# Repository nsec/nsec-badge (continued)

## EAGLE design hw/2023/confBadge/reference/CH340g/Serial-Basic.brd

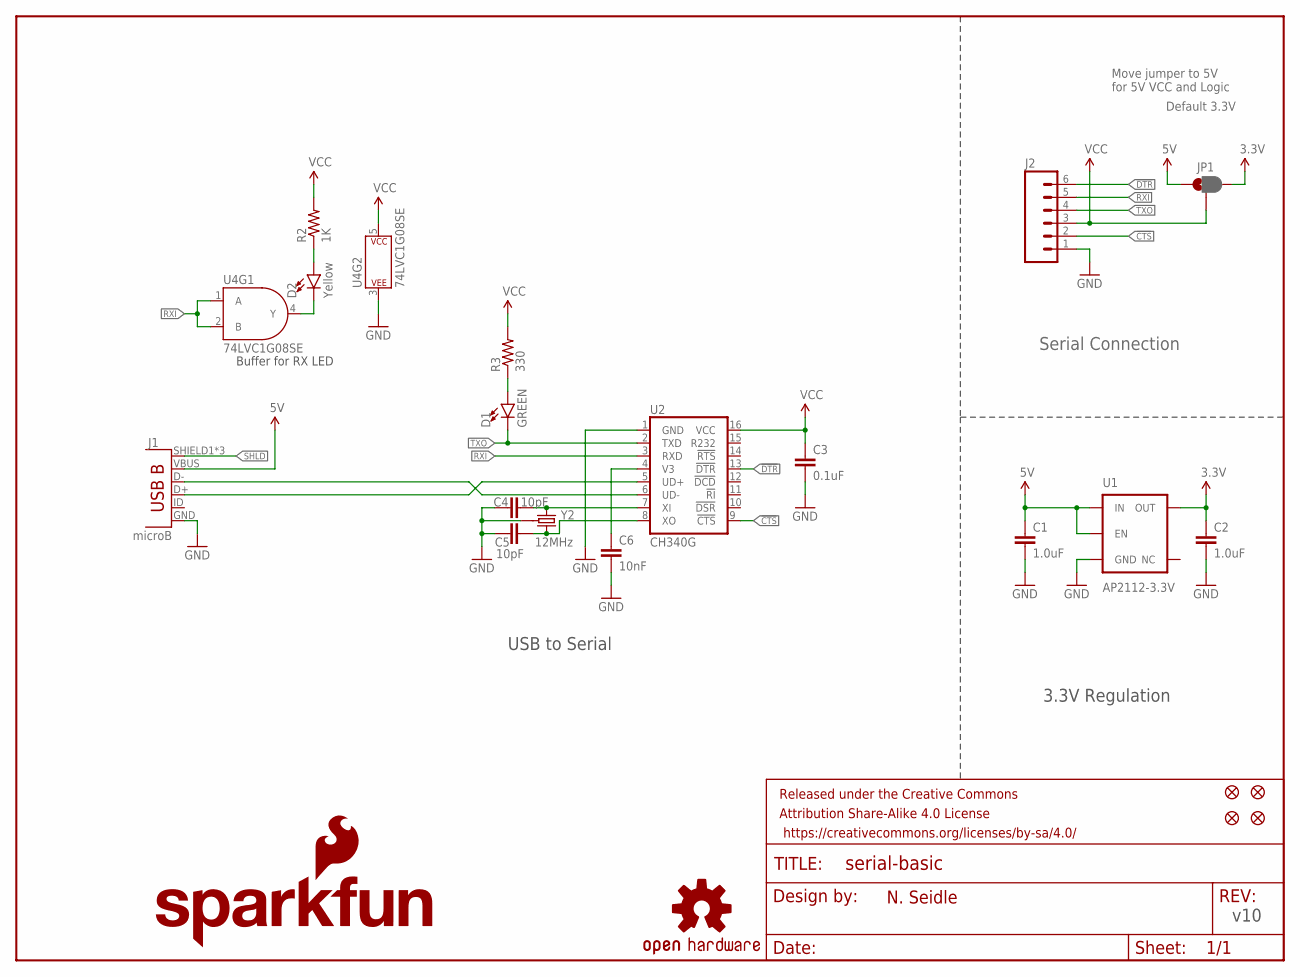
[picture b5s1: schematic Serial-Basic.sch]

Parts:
C1, C2: 1.0uF; 0603-CAP
C3: 0.1uF; 0603-CAP
C4, C5: 10pF; 0603-CAP
C6: 10nF; 0603-CAP
D1: GREEN; LED-0603
D2: Yellow; LED-0603
FRAME1: FRAME-LETTER; CREATIVE_COMMONS
J1: microB; USB-B-MICRO-SMD_V03
J2: M06SMD-FEMALE-V2; 1X06-SMD-FEMALE-V2
JP1: JUMPER-PAD-3-2OF3_NC_BY_PASTE; PAD-JUMPER-3-2OF3_NC_BY_PASTE_YES_SILK_FULL_BOX
JP3, JP4, JP5, JP6: FIDUCIAL1X2; FIDUCIAL-1X2
LOGO1: OSHW-LOGOS; OSHW-LOGO-S
LOGO2: SFE_LOGO_FLAME.1_INCH; SFE_LOGO_FLAME_.1
LOGO3: SFE_LOGO_NAME.1_INCH; SFE_LOGO_NAME_.1
R2: 1K; 0603-RES
R3: 330; 0603-RES
U1: AP2112-3.3V; SOT23-5
U2: CH340G; SO016
U4: 74LVC1G08SE; SOT353
Y2: 12MHz; CRYSTAL-SMD-3.2X2.5

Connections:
3.3V: C2.1, JP1.3, U1.5 (OUT)
5V: C1.1, J1.VBUS, JP1.1, U1.1 (IN), U1.3 (EN)
!CTS: J2.2, U2.9 (!CTS)
!DTR: J2.6, U2.13 (!DTR)
GND: C1.2, C2.2, C3.2, C4.1, C5.1, C6.2, J1.GND, J2.1, U1.2 (GND), U2.1 (GND), U4.3 (P$V-), Y2.2 (GND), Y2.4 (GND)
unnamed: D1.A, R3.1
unnamed: D2.A, R2.1
unnamed: C5.2, U2.8 (XO), Y2.3 (2)
unnamed: C4.2, U2.7 (XI), Y2.1
unnamed: D2.C, U4.4 (Y)
unnamed: J1.D-, U2.6 (UD-)
unnamed: J1.D+, U2.5 (UD+)
RXI: J2.5, U2.3 (RXD), U4.1 (A), U4.2 (B)
SHLD: J1.SHIELD1 (SHIELD), J1.SHIELD2 (SHIELD), J1.SHIELD3 (SHIELD)
TXO: D1.C, J2.4, U2.2 (TXD)
V3: C6.1, U2.4 (V3)
VCC: C3.1, J2.3, JP1.2, R2.2, R3.2, U2.16 (VCC), U4.5 (P$V+)

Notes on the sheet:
Default 3.3V
v10
USB to Serial
3.3V Regulation
N. Seidle
Move jumper to 5V for 5V VCC and Logic
Buffer for RX LED
Serial Connection

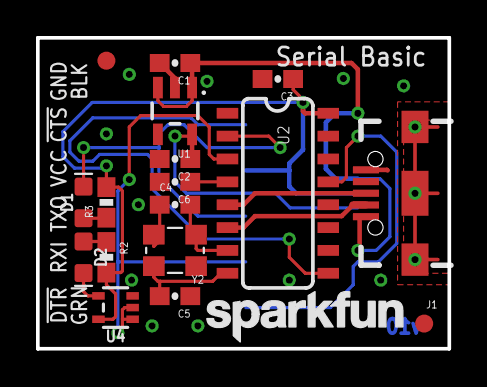
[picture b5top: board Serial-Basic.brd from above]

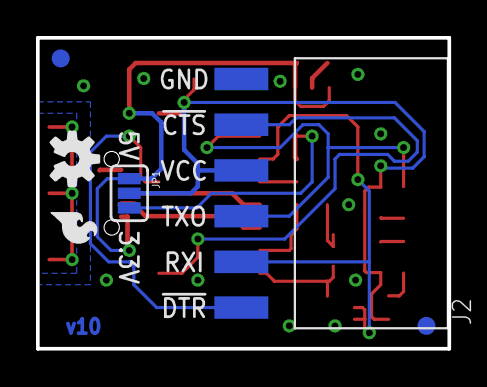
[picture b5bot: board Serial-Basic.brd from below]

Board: 2 copper layers, 22.9 x 17.3 mm, 25 parts (6 on the bottom side), 17 nets.

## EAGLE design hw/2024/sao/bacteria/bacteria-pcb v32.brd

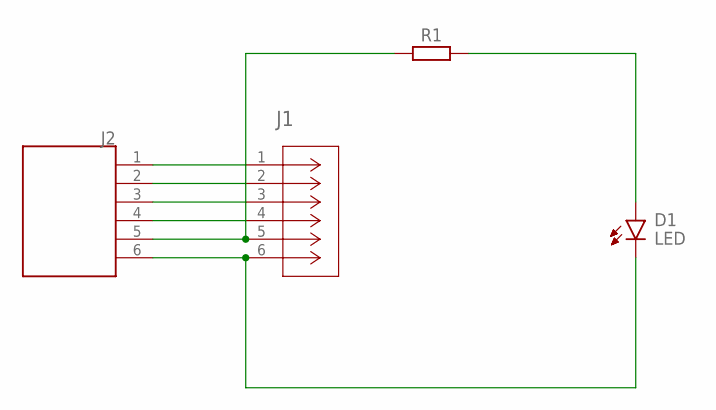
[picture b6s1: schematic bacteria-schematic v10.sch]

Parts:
D1: LED; LEDC3216X75N_FLAT-R
J1: M20-8760342CONN6_M20-8760342_HRW; CONN6_M20-8760342_HRW
J2: SAOPADBREAKOUT
R1: R_CHIP-1206(3216-METRIC); RESC3216X70

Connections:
3V3: J1.5, J2.5, R1.1
GND: D1.C, J1.6, J2.6
GPIO1: J1.1, J2.1
GPIO2: J1.2, J2.2
unnamed: D1.A, R1.2
SCL: J1.4, J2.4
SDA: J1.3, J2.3

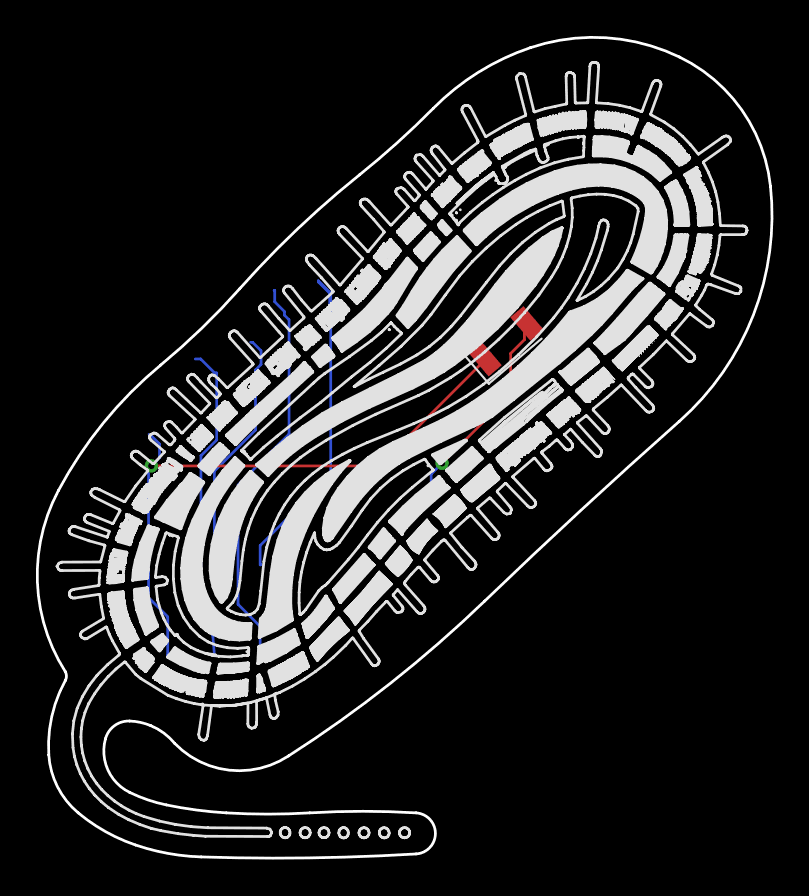
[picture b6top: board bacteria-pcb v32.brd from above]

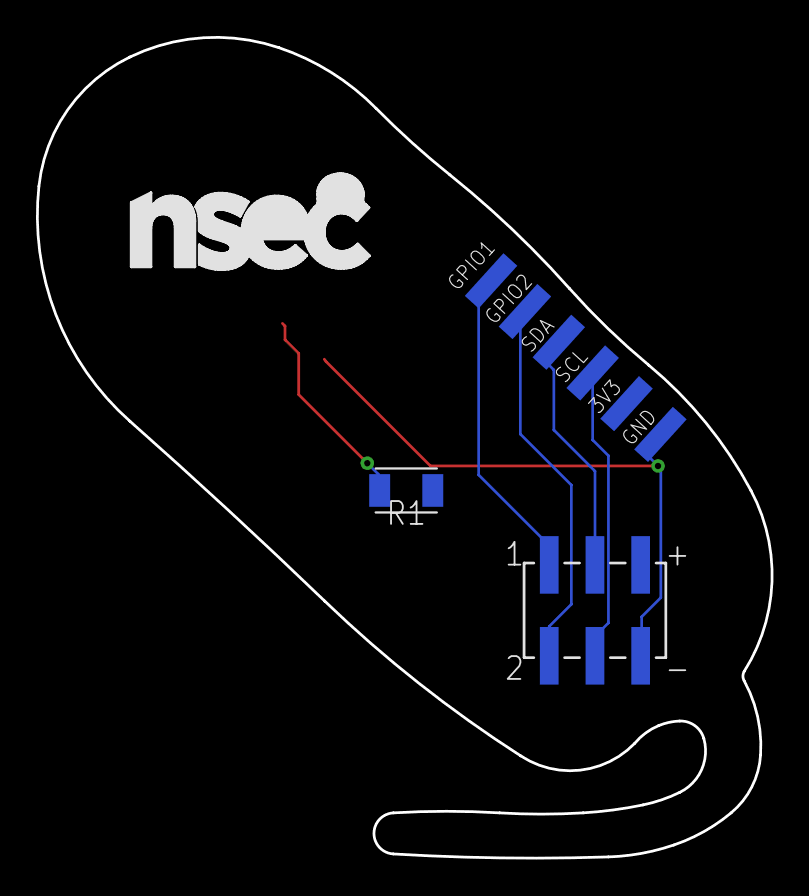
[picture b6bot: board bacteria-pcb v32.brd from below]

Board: 2 copper layers, 40.8 x 45.6 mm, 4 parts (3 on the bottom side), 7 nets.

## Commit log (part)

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2024-02-15 fixing pins to match badge
2024-02-16 oops forgot the schema
2024-02-18 Few nitpicks fixes.
2024-02-19 fix CMake to work on the first time
2024-02-25 Update `mb_example` README.md
    remove duplicates
2024-03-13 Create Gerber_SAO-ctf-2024_PCB_SAO-ctf-2024_2024-02-25.zip
    file used for ordering prototype number 1
2024-03-20 scheduling: use configuration for default task attributes
2024-03-20 Enable symbolic backtraces on crash
    Configure the conference build to enable backtraces with full symbol
    resolution from the monitor command. It provides this type of output
    when a crash occurs:
    Hello from dummy task
    abort() was called at PC 0x42007177 on core 0
    Backtrace: 0x4037582e:0x3fc99b80 0x40379b69:0x3fc99ba0 0x4037f5c6:0x3fc99bc0 0x42007177:0x3fc99c30 0x420071ac:0x3fc99c50 0x42007287:0x3fc99c70 0x42001e0b:0x3fc99c90 0x42001e31:0x3fc99cc0 0x42001e51:0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
2024-03-20 Fix: ctf firmware build
    * Add the missing variables in the components CMakeLists.txt files
    * Vendor the 'mdns' and 'esp-modbus' components
    * Remove the incompatible metadata in mdns/idf_component.yml
2024-03-22 Bug Fix - Rename "button" folder to avoid conflict with "espressif__button" component (#452)
    * button: rename folder to avoid conflict with "espressif__button" component
    When adding the "espressif/button" component, build error occured.
    Two different errors are reported (depending how the component is added).
    Error 1:
    CMake Error at C:/Users/<username>/.platformio/packages/framework-espidf/tools/cmake/component.cmake:479 (add_library):
    Target "__idf_button" links to itself.
2024-03-23 buttons: add debugging information
    Add debugging information that are sent to the console on IOT button events.
2024-03-26 Set up the proper default baud rate for pio
2024-04-03 Make gcc hgappy with console.cpp
2024-04-03 watcher: add support to test the integration with the badge button events
    Add support to test the watcher integration with the badge button events
    callback functionality.
    The test function is printing the button event to the debugging console.
    The debugging code is disable by default (conditional compile).
2024-04-03 badge: add support to test the integration with the badge button events
    Add support to test the badge module integration with the badge button
    events callback functionality.
    The test function is printing the button event to the debugging console.
    The debugging code is disable by default (conditional compile).
2024-04-14 Flash each firmware flavor to its own partition
    Add a partitions table and the proper flash offsets in platformio.ini.
2024-04-14 removing ota_operations.cpp from challenges
2024-04-21 Fix: strip animator: handle progress bar decrease transitions
    The progress bar animation assumed that it could only move forwards.
    However, it can effectively go backwards when a pairing attempt fails
    and is retried before going through an "idle" animation cycle.
2024-04-21 Improve communication logging
2024-04-21 Temporary workaround for badge pairing bug
2024-04-21 badge: add support to test the scroll LEDs pattern
    Add support to test the scroll LEDs pattern using the left/right badge button
    The test function is printing the related LEDs patterninfo to the debugging console.
    The debugging code is disable by default (conditional compile).
2024-04-21 badge: update social level and health index selected display animation
    Select the specific animation for the social level and the health index
    when the communication is in "idle" state.
2024-04-21 README.md: add documentation for "upload-port" option.
    Add documentation to select which port will be use to upload the image
    to be flash on the badge.
    This option is really useful to select which badge to flash when multiple
    badges are connected to the PC.
2024-04-22 plug me flag using hmac
2024-04-23 adding crypto_bad flag
2024-04-24 Remove empty button task
2024-04-24 Move health bar display logic to animation completed animator
2024-04-27 Fix: buttons sometimes not properly initialized
    It seems that FreeRTOS and/or the ESP-IDF SDK are not completely
    initialized before entering app_main(). Since the badge object is
    global, it's constructor runs before the control is handed over to
    app_main().
    The badge instance is moved within the scope of app_main() which causes
    the initialization to happen within a proper FreeRTOS task (and not the
2024-04-28 minor text
2024-04-28 Set pio lib finding algo to deep+ for ctf and addon
    Change libraries search algorithm to deep+ to follow pre-processor
    commands:
    https://docs.platformio.org/en/stable/librarymanager/ldf.html#dependency-finder-mode
    Fix #467
2024-04-30 Add system commands
    Currently implemented are 'reboot' and 'factory_reset'.
2024-05-02 updating ota README for pio
2024-05-02 Make the logging level of button watcher configurable
2024-05-02 Add the capability to store and retrieve badge IDs from NVS
2024-05-04 Logic for button press
2024-05-04 Script to generate random button patterns for levels
2024-05-04 Tweaking the read with timeout to be on error only
2024-05-04 Registering the buttons
2024-05-04 Adds ir command
2024-05-05 Clear the leds on soft reboot
    When using 'esp_restart()' to do a soft reboot, the leds stay powered
    and thus retain the last frame until the badge is either hard reset or
    reboot in the 'conf' firmware.
    Clear the leds before calling esp_restart().
2024-05-05 strip_animator: force social level display brightness in idle mode
    The social level display, while the badge is in "idle" mode is
    almost not visible.
    Increase the LEDs brightness for the display of the social level
    while in "idle" mode.
2024-05-05 Lower log level of conf firmware
    This makes the console much more usable.
2024-05-07 Increase the speed of the network
    While testing 'pairing' with 10 badges we noticed that sometimes the
    network would timeout. Significantly increase the speed of the network
    as the values were based on the limits of last years badge based on the
    ATmega328PB.
2024-05-07 Fix: badge: underflow when cycling animations
    Copied from Sylvain Lemieux's commit message addressing the same
    problem:
    When the badge is running for the first time (i.e. social level 0) or is factory reset,
    the selected animation is set to 255 (see log bellow).
    [badge:info 0] Button event: button=LEFT, event=SINGLE_CLICK
    [badge:info 0] Cycling selected animation: direction=-1, original_animation_id=0, new_animation_id=-1
2024-05-07 strip_animator: move social level display on lower leds
    The shield is not as translucid in the top portion (large white area).
    Move the social level display on the lower LEDs to improve visibility.
2024-05-08 Add a 'clear' command to the console
    Add a 'clear' command to reset the console and print the banner.
2024-05-09 Clean-up: badge: use the badge method directly instead of global
    on_button_event is a badge method, so it can access the other methods
    without using the global `the_badge` variable.
2024-05-09 badge: clean-up - remove bitfield restrictions for nb badges during sync
    Removed the unnecessary bitfield restrictions for the number of badges limit (32)
    during synchronization, caused by the limitations of the AVR badge used last year.
2024-05-10 Add some leeway for what's considered multiple clicks
2024-05-10 Lower the priority of the debug led task
    According to the SDK documentation, low priority tasks should be set
    between 1-3.
2024-05-10 Fix: badge: uninitialized message direction used to enqueue messages
    The right-most badge sometimes fails to pair with the following error
    log: "Failed to enqueue message: attempted to send a message out of bounds".
    This occurs when, for example, a badge at the right-most end of a chain
    attempts to send a message to its right-hand neighbor. This is
    necessarily an internal error.
    _direction is not initialized for left-most and right-most badges since
2024-05-10 log unexpected messages
2024-05-11 fix: init nvs before badge constructor
2024-05-11 master-flasher: 8 badges
    Add support to flash 8 badges at a time.
2024-05-11 removing dbg_led_task because it crashes ota
2024-06-28 Adding Badge and SAO for nsec2024
2024-12-15 Remove addon from CI
2025-01-26 removing refs to addon firmware from 2024
2025-01-26 Remove external off-the-addon components
2025-01-26 Reduce partitions offset to make it under 4MB
2025-01-26 Update platformio.yml for plaintext flag check
2025-01-26 working model of centralized ssd1306/smartled + initial port of quantum challenge code
2025-02-03 QKD badge framework with base def and decrypt
2025-02-17 added initial noisy qkd2 functionality for receive/nvs
2025-03-23 Tweaks and final pre-QA adjustments
2025-03-28 watcher: fix error when creating buttons callback
    Commit 8dbb02f8 updated the button available on the 2025 badge.
    When creating the watcher instance, the following error occurred:
    [Button watcher:info 0] Setting up button callbacks
    E (3095) button: iot_button_register_cb(535): Pointer of handle is invalid
    abort() was called at PC 0x4203814d on core 0
    Fixed the issue by updating the number of buttons callback that
2025-03-30 Adjusting logo based on group request
2025-04-01 badge: update button selection when pressing input
    The button available for the 2025 conference badge is different tha
    the 2024 badge. Update the code accordingly.
2025-04-01 badge: update logger output when cycling animation
    Update logger output when cycling animation to ensure the logging output
    is fitting on a single line.
2025-04-01 badge: replace health mapping by clearance level mapping
    Replace the support for social level to health index mapping by
    social level to clearance level mapping.
2025-04-01 badge: remove "pairing completed animator" related code
    Remove the code related to the "pairing completed animator" capabilities that
    was present in the badge module (2024 conference badge code).
    This commit is compiling, but will not run properly on the badge.
    NOTE:
    * This commit is part of the cleanup used to to create the initial baseline
    for the 2025 conference badge module.
2025-04-08 badge: display sponsor count on LCD
    Add support to display the sponsor count on the
    LCD screen 1.
    # Conflicts:
    # components/badge/badge.cpp
2025-04-08 badge: add support for "sponsor" flag and count
    Add support to load/save "sponsor flag" from/to persistence storage.
    Also retrieve the sponsor flag at power-on (load config)
    and compute the sponsor total count, from the flag.
2025-04-10 adding hash for reverse resistant approach
2025-04-13 badge: display "IR exchange" screen when process trigger
    As soon as the long press of the "OK" button is detected, display
    the "IR Exchange" screen to make it clear to process is started.
2025-04-13 Configuration related to IR
2025-05-01 bus reset pre-init to account for hw oddities
2025-05-01 Badge - cleanup and update (#576)
    * strip_animator: remove unused code
    Removed unused code from the 2023/2024 strip animator badge code.
    * strip_animator: add specific logger config
    Add support to be able to control the logging capability of the
    strip animator individually.
    * config_store: fix spacing alignment
2025-05-02 badge: update formula when applying score
    For 2025, the badges are sync in pair; update the level based
    on the current social level (going faster initially).
    Update table:
    * Current social level 20 or less -> +5 level.
    * Current social level 75 or less -> +4 level.
    * Current social level 125 or less -> +3 level.
2025-05-03 Fixed non-serial delay output and visual screen aids for qkd track (#580)
    * Fixed non-serial delay output and visual screen aids for qkd track
    * fixing comments on pr
2025-05-03 Work-in-progress for the IR communication
2025-05-03 Delay ACK half a second, and set initial delay to 2 sec
2025-05-03 More tweaks
2025-05-03 Helper to check if ID exists in badge
2025-05-03 Rewrite of network handler
2025-05-04 last golden image binary and universal flashing script
2025-05-11 minor bug solving
2025-05-12 reregister codenames command
2025-05-12 small formatting fix
2025-05-13 NSEC 2025 - Golden images + flashing instructions/scripts
2025-07-02 Pre-release 2025 public clean up
